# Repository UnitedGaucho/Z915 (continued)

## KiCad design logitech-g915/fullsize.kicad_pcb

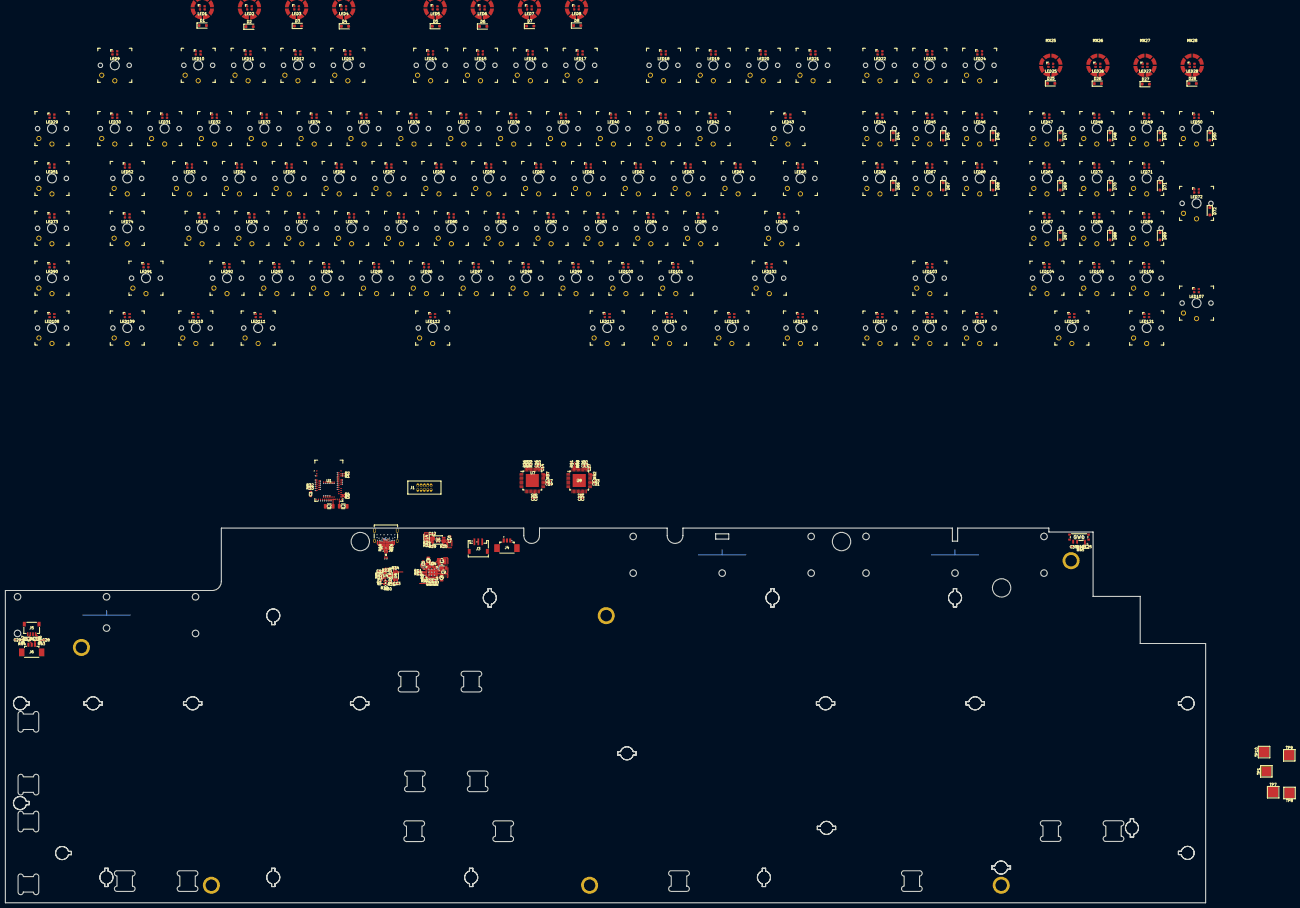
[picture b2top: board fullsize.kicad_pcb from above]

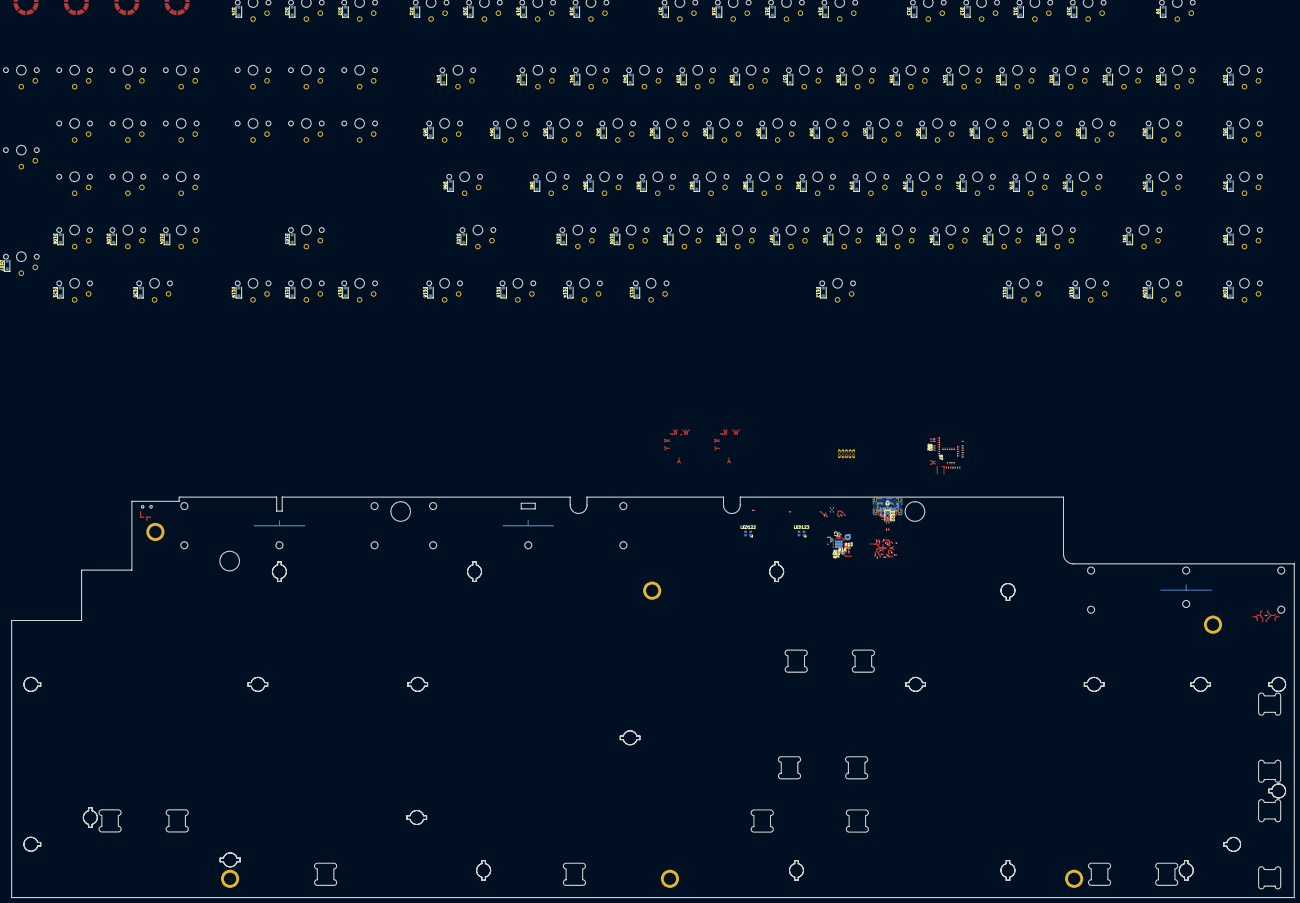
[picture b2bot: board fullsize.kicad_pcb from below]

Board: 4 copper layers, 458.6 x 143.2 mm, 477 parts (104 on the bottom side), 258 nets.

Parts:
C1, C28, C29, C30: 10nF; C_0603_1608Metric
C2, C3: 10uF; C_1206_3216Metric
C4: 47nF; C_0402_1005Metric
C5: 1uF; C_0603_1608Metric
C6, C8: 10uF; C_0805_2012Metric
C7: 4.7uF; C_0402_1005Metric
C9: 22uF; C_0805_2012Metric
C10: 4.7uF; C_0805_2012Metric
C11, C13, C14, C19, C20, C21, C22, C27: 0.1uF; C_0402_1005Metric
C12: 10uF; C_0402_1005Metric
C15, C16, C17, C18, C23, C24, C25, C26: 0.47uF; C_0402_1005Metric
C31: 4.7nF; C_0402_1005Metric
D1, D2, D3, D4, D5, D6, D7, D8, D9, D10, D11, D12, D13, D14, D15, D16, D17, D18, D19, D20, D21, D22, D23, D24, D25, D26, D27, D28, D29, D30, D31, D32, D33, D34, D35, D36, D37, D38, D39, D40, D41, D42, D43, D44, D45, D46, D47, D48, D49, D50, D51, D52, D53, D54, D55, D56, D57, D58, D59, D60, D61, D62, D63, D64, D65, D66, D67, D68, D69, D70, D71, D72, D73, D74, D75, D76, D77, D78, D79, D80, D81, D82, D83, D84, D85, D86, D87, D88, D89, D90, D91, D92, D93, D94, D95, D96, D97, D98, D99, D100, D101, D102, D103, D104, D105, D106, D107, D108, D109, D110, D111, D112, D113, D114, D115, D116, D117, D118, D119, D120, D121: B140S1F-7; D_SOD-123F
D122: SZSMF6L5.0AT3G; D_SOD-123F
D123, D124, D125: ESD5Z3; D_SOD-523
J1: Conn_02x05_Odd_Even; DB_CONN
J3: 648103131822
J4, J6: 10114830-11103LF; AMPHENOL_10114830-11103LF
J5: G846A04100Y1EU; AMPHENOL_G846A04100Y1EU
J7: USB_C_Receptacle_USB2.0_16P; AMPHENOL_GSB1C411101DS1HR
L1: 60R@100MHz; L_0603_1608Metric
L2: L_Coupled; FIL_ACM2012-900-2P-T001
L3: 1.5uH; L_1008_2520Metric
L4: 2.2uH; L_Murata_DFE201610P
LED1, LED2, LED3, LED4, LED5, LED6, LED7, LED8, LED9, LED10, LED11, LED12, LED13, LED14, LED15, LED16, LED17, LED18, LED19, LED20, LED21, LED22, LED23, LED24, LED25, LED26, LED27, LED28, LED29, LED30, LED31, LED32, LED33, LED34, LED35, LED36, LED37, LED38, LED39, LED40, LED41, LED42, LED43, LED44, LED45, LED46, LED47, LED48, LED49, LED50, LED51, LED52, LED53, LED54, LED55, LED56, LED57, LED58, LED59, LED60, LED61, LED62, LED63, LED64, LED65, LED66, LED67, LED68, LED69, LED70, LED71, LED72, LED73, LED74, LED75, LED76, LED77, LED78, LED79, LED80, LED81, LED82, LED83, LED84, LED85, LED86, LED87, LED88, LED89, LED90, LED91, LED92, LED93, LED94, LED95, LED96, LED97, LED98, LED99, LED100, LED101, LED102, LED103, LED104, LED105, LED106, LED107, LED108, LED109, LED110, LED111, LED112, LED113, LED114, LED115, LED116, LED117, LED118, LED119, LED120, LED121, LED122, LED123: ASMB-LTD3; LED_ASMB-LTD3
MX1, MX2, MX3, MX4, MX5, MX6, MX7, MX8, MX25, MX26, MX27, MX28: 1.00u; Membrane-G915
MX9, MX10, MX11, MX12, MX13, MX14, MX15, MX16, MX17, MX18, MX19, MX20, MX21, MX22, MX23, MX24, MX29, MX30, MX31, MX32, MX33, MX34, MX35, MX36, MX37, MX38, MX39, MX40, MX41, MX42, MX43, MX44, MX45, MX46, MX47, MX48, MX49, MX50, MX51, MX52, MX53, MX54, MX55, MX56, MX57, MX58, MX59, MX60, MX61, MX62, MX63, MX64, MX65, MX66, MX67, MX68, MX69, MX70, MX71, MX72, MX73, MX74, MX75, MX76, MX77, MX78, MX79, MX80, MX81, MX82, MX83, MX84, MX85, MX86, MX87, MX88, MX89, MX90, MX91, MX92, MX93, MX94, MX95, MX96, MX97, MX98, MX99, MX100, MX101, MX102, MX103, MX104, MX105, MX106, MX107, MX108, MX109, MX110, MX111, MX112, MX113, MX114, MX115, MX116, MX117, MX118, MX119, MX120, MX121: 1.00u; SW_Kailh_Choc_V1_THT
Q1: NTA4153NT1G; SOT-416
R1, R2, R3, R4: 22; R_0402_1005Metric
R5, R6: 4.7k; R_0402_1005Metric
R7: 10k; R_0402_1005Metric
R8, R9, R26, R27, R28, R30, R43, R44, R45: 100k; R_0402_1005Metric
R10, R11, R12, R13, R17, R20, R21, R23, R24, R25: 0; R_0402_1005Metric
R14: 845; R_0402_1005Metric
R15, R16: 5.1k; R_0402_1005Metric
R18: 5.23k; R_0402_1005Metric
R19: 30.9k; R_0402_1005Metric
R22: 887k; R_0402_1005Metric
R29: 21.5k; R_0402_1005Metric
R31: 316; R_0402_1005Metric
R32: 1M; R_0402_1005Metric
R33: 499k; R_0402_1005Metric
R34: 487; R_0402_1005Metric
R35: 953; R_0402_1005Metric
R36, R38, R39, R40, R41, R49: 100K; R_0402_1005Metric
R37, R42: 20k; R_0402_1005Metric
R46, R47, R48: 1k; R_0402_1005Metric
S1: Open Hardware; OSHW-Logo
S2: BLE-symbol
S3: ZMK_logo
SW1: PCM12SMTR; SW_PCM12SMTR
TP1, TP7, TP8, TP9, TP10: TouchPoint; TestPoint_Pad_4.0x4.0mm
U1: MDBT50Q-1MV2/MEN; Raytac_MDBT50Q
U2: BQ25616J; Texas_RTW_WQFN-24-1EP_4x4mm_P0.5mm_EP2.7x2.7mm_ThermalVias
U3: TPD4E05U06DQAR; USON-10
U4: TUSB320; Texas_X2QFN-12_1.6x1.6mm_P0.4mm
U5: TPS62842DGR; HVSSOP-8-1EP_3x3mm_P0.65mm_EP1.57x1.89mm
U6: TS5A23167; VSSOP-8_2.3x2mm_P0.5mm
U7, U8: IS31FL3733-TQ; TQFP-48-1EP_7x7mm_P0.5mm_EP5x5mm

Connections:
+3V0: C2.1, C11.2, C12.1, C13.1, C14.1, C15.1, C16.1, C25.1, C26.1, C27.1, J1.1, L4.2, R5.2, R6.2, R7.2, R26.2, R27.2, R28.2, R39.2, R40.2, R43.2, R44.2, R45.2, U1.28 (VDD), U1.30 (VDDH), U4.12 (VDD), U5.1 (VOS), U6.8 (V+), U7.37 (AVCC), U7.38 (DVCC), U7.39 (VIO), U8.37 (AVCC), U8.38 (DVCC), U8.39 (VIO)
/COL1: MX29.2 (B), MX51.2 (B), MX73.2 (B), MX90.2 (B), MX108.2 (B), U1.3 (P1.10)
/COL2: MX9.2 (B), MX30.2 (B), MX52.2 (B), MX74.2 (B), MX91.2 (B), MX109.2 (B), MX110.2 (B), U1.4 (P1.11)
/COL3: MX31.2 (B), MX53.2 (B), MX75.2 (B), MX92.2 (B), MX111.2 (B), U1.5 (P1.12)
/COL4: MX10.2 (B), MX32.2 (B), MX54.2 (B), MX76.2 (B), MX93.2 (B), U1.6 (P1.13)
/COL5: MX11.2 (B), MX33.2 (B), MX55.2 (B), MX77.2 (B), MX94.2 (B), U1.7 (P1.14)
/COL6: MX12.2 (B), MX34.2 (B), MX56.2 (B), MX78.2 (B), MX95.2 (B), U1.8 (P1.15)
/COL7: MX13.2 (B), MX35.2 (B), MX57.2 (B), MX79.2 (B), MX96.2 (B), MX112.2 (B), U1.9 (P0.03)
/COL8: MX36.2 (B), MX58.2 (B), MX80.2 (B), MX97.2 (B), U1.10 (P0.29)
/COL9: MX14.2 (B), MX37.2 (B), MX59.2 (B), MX81.2 (B), MX98.2 (B), U1.11 (P0.02)
/COL10: MX15.2 (B), MX38.2 (B), MX60.2 (B), MX82.2 (B), MX99.2 (B), MX113.2 (B), U1.12 (P0.31)
/COL11: MX16.2 (B), MX39.2 (B), MX61.2 (B), MX83.2 (B), MX100.2 (B), MX114.2 (B), U1.13 (P0.28)
/COL12: MX17.2 (B), MX40.2 (B), MX62.2 (B), MX84.2 (B), MX101.2 (B), U1.16 (P0.27)
/COL13: MX18.2 (B), MX41.2 (B), MX63.2 (B), MX85.2 (B), MX115.2 (B), U1.17 (P0.00)
/COL14: MX19.2 (B), MX42.2 (B), MX64.2 (B), MX86.2 (B), MX102.2 (B), MX116.2 (B), U1.18 (P0.01)
/COL15: MX20.2 (B), MX21.2 (B), MX43.2 (B), MX65.2 (B), U1.19 (P0.26)
/COL16: MX22.2 (B), MX44.2 (B), MX66.2 (B), MX117.2 (B), U1.20 (P0.04)
/COL17: MX23.2 (B), MX45.2 (B), MX67.2 (B), MX103.2 (B), MX118.2 (B), U1.21 (P0.05)
/COL18: MX24.2 (B), MX46.2 (B), MX68.2 (B), MX119.2 (B), U1.22 (P0.06)
/COL19: MX47.2 (B), MX69.2 (B), MX87.2 (B), MX104.2 (B), MX120.2 (B), U1.23 (P0.07)
/COL20: MX48.2 (B), MX70.2 (B), MX88.2 (B), MX105.2 (B), U1.24 (P0.08)
/COL21: MX49.2 (B), MX71.2 (B), MX89.2 (B), MX106.2 (B), MX121.2 (B), U1.25 (P1.08)
/COL22: MX50.2 (B), MX72.2 (B), MX107.2 (B), U1.26 (P1.09)
/DB_SWDCLK: J1.4, R2.1
/DB_SWDIO: J1.2, R1.1
/INTB1: R39.1, U1.48 (P0.24), U7.45 (~INTB)
/INTB2: R40.1, U1.49 (P0.25), U8.45 (~INTB)
/NRF_D+: R4.2, U1.35 (D+)
/NRF_D-: R3.2, U1.34 (D-)
/PWR: C30.1, R45.1, R48.1, U1.50 (P1.02)
/ROW0: D9.1 (K), D10.1 (K), D11.1 (K), D12.1 (K), D13.1 (K), D14.1 (K), D15.1 (K), D16.1 (K), D17.1 (K), D18.1 (K), D19.1 (K), D20.1 (K), D21.1 (K), D22.1 (K), D23.1 (K), D24.1 (K), U1.56 (P1.04)
/ROW1: D29.1 (K), D30.1 (K), D31.1 (K), D32.1 (K), D33.1 (K), D34.1 (K), D35.1 (K), D36.1 (K), D37.1 (K), D38.1 (K), D39.1 (K), D40.1 (K), D41.1 (K), D42.1 (K), D43.1 (K), D44.1 (K), D45.1 (K), D46.1 (K), D47.1 (K), D48.1 (K), D49.1 (K), D50.1 (K), U1.57 (P1.06)
/ROW2: D51.1 (K), D52.1 (K), D53.1 (K), D54.1 (K), D55.1 (K), D56.1 (K), D57.1 (K), D58.1 (K), D59.1 (K), D60.1 (K), D61.1 (K), D62.1 (K), D63.1 (K), D64.1 (K), D65.1 (K), D66.1 (K), D67.1 (K), D68.1 (K), D69.1 (K), D70.1 (K), D71.1 (K), D72.1 (K), U1.58 (P1.07)
/ROW3: D73.1 (K), D74.1 (K), D75.1 (K), D76.1 (K), D77.1 (K), D78.1 (K), D79.1 (K), D80.1 (K), D81.1 (K), D82.1 (K), D83.1 (K), D84.1 (K), D85.1 (K), D86.1 (K), D87.1 (K), D88.1 (K), D89.1 (K), U1.59 (P1.05)
/ROW4: D90.1 (K), D91.1 (K), D92.1 (K), D93.1 (K), D94.1 (K), D95.1 (K), D96.1 (K), D97.1 (K), D98.1 (K), D99.1 (K), D100.1 (K), D101.1 (K), D102.1 (K), D103.1 (K), D104.1 (K), D105.1 (K), D106.1 (K), D107.1 (K), U1.60 (P1.03)
/ROW5: D108.1 (K), D109.1 (K), D110.1 (K), D111.1 (K), D112.1 (K), D113.1 (K), D114.1 (K), D115.1 (K), D116.1 (K), D117.1 (K), D118.1 (K), D119.1 (K), D120.1 (K), D121.1 (K), U1.61 (P1.01)
/ROWM: D1.1 (K), D2.1 (K), D3.1 (K), D4.1 (K), D5.1 (K), D6.1 (K), D7.1 (K), D8.1 (K), D25.1 (K), D26.1 (K), D27.1 (K), D28.1 (K), U1.47 (P1.00)
/SCL: R6.1, U1.46 (P0.22), U7.42 (SCL), U8.42 (SCL), U8.43 (ADDR1)
/SDA: R5.1, U1.45 (P0.23), U7.41 (SDA), U8.41 (SDA)
/SDB: R38.2, R49.2, U1.44 (P0.20), U7.46 (~SDB), U8.46 (~SDB)
/USB and Power Mgmt/BATT_NTC: C31.1, J3.2, J4.3, R18.1, R19.2, U2.11 (TS)
/USB and Power Mgmt/CC1: J7.A5 (CC1), R15.2, R20.2, U3.5 (D2-), U3.6 (NC)
/USB and Power Mgmt/CC2: J7.B5 (CC2), R16.2, R21.2, U3.1 (IO1), U3.10 (NC)
/USB and Power Mgmt/ILIM: R35.2, U2.8 (ILIM), U6.1
/USB and Power Mgmt/OUT1: R26.1, U4.7 (SDA/OUT1), U6.7
/USB and Power Mgmt/OUT2: R28.1, U4.8 (SCL/OUT2), U6.3
/USB and Power Mgmt/REGN: C7.1, R18.2, U2.22 (REGN)
/USB and Power Mgmt/TVS_D+: J7.A6 (D+), J7.B6 (D+), L2.2, U3.2 (IO2), U3.9 (NC)
/USB and Power Mgmt/TVS_D-: J7.A7 (D-), J7.B7 (D-), L2.1, U3.4 (D2+), U3.7 (NC)
/USB and Power Mgmt/U2-D+: R11.1, U2.3 (D+)
/USB and Power Mgmt/U2-D-: R12.1, U2.4 (D-)
/USB_D+: L2.3, R4.1, R11.2
/USB_D-: L2.4, R3.1, R12.2
/VBATT_nRF: C1.1, R32.1, R33.2, U1.14 (AIN6)
/VBUS: C3.1, C5.1, D122.1 (K), J1.5, J7.A4B9 (VBUS), J7.B4A9 (VBUS), Q1.G, R22.2, R30.2, U1.32 (VBUS), U2.1 (VAC), U2.24 (VBUS)
/VCOM-UART_RX: J1.8, U1.43 (P0.21)
/VCOM-UART_TX: J1.7, U1.42 (P0.19)
/VOL_A: C28.1, R43.1, R46.1, U1.52 (P0.09)
/VOL_B: C29.1, R44.1, R47.1, U1.54 (P0.10)
/indicators_controls/Vol_A: D123.1 (K), J5.1, J6.3, R46.2
/indicators_controls/Vol_B: D124.1 (K), J5.3, J6.2, R47.2
/rgb-led_matrix/C1.1: LED29.1 (A), LED30.1 (A), LED51.1 (A), LED52.1 (A), U7.16 (CS1)
/rgb-led_matrix/C1.2: LED9.1 (A), LED31.1 (A), LED53.1 (A), U7.17 (CS2)
/rgb-led_matrix/C1.3: LED1.1 (A), LED10.1 (A), LED32.1 (A), LED54.1 (A), U7.18 (CS3)
/rgb-led_matrix/C1.4: LED2.1 (A), LED11.1 (A), LED33.1 (A), LED55.1 (A), U7.19 (CS4)
/rgb-led_matrix/C1.5: LED3.1 (A), LED12.1 (A), LED34.1 (A), LED56.1 (A), U7.21 (CS5)
/rgb-led_matrix/C1.6: LED4.1 (A), LED13.1 (A), LED35.1 (A), LED57.1 (A), U7.22 (CS6)
/rgb-led_matrix/C1.7: LED5.1 (A), LED14.1 (A), LED36.1 (A), LED58.1 (A), U7.23 (CS7)
/rgb-led_matrix/C1.8: LED6.1 (A), LED15.1 (A), LED37.1 (A), LED59.1 (A), U7.24 (CS8)
/rgb-led_matrix/C1.9: LED7.1 (A), LED16.1 (A), LED38.1 (A), LED60.1 (A), U7.25 (CS9)
/rgb-led_matrix/C1.10: LED8.1 (A), LED17.1 (A), LED39.1 (A), LED61.1 (A), U7.26 (CS10)
/rgb-led_matrix/C1.11: LED40.1 (A), LED41.1 (A), LED62.1 (A), LED63.1 (A), U7.27 (CS11)
/rgb-led_matrix/C1.12: LED18.1 (A), LED19.1 (A), LED122.1 (A), LED123.1 (A), U7.28 (CS12)
/rgb-led_matrix/C1.13: LED20.1 (A), LED21.1 (A), LED42.1 (A), LED64.1 (A), U7.30 (CS13)
/rgb-led_matrix/C1.14: LED22.1 (A), LED43.1 (A), LED44.1 (A), LED65.1 (A), U7.31 (CS14)
/rgb-led_matrix/C1.15: LED23.1 (A), LED45.1 (A), LED67.1 (A), LED103.1 (A), U7.32 (CS15)
/rgb-led_matrix/C1.16: LED66.1 (A), LED117.1 (A), LED118.1 (A), U7.33 (CS16)
/rgb-led_matrix/C2.1: LED73.1 (A), LED90.1 (A), LED108.1 (A), LED109.1 (A), U8.16 (CS1)
/rgb-led_matrix/C2.2: LED74.1 (A), LED91.1 (A), LED110.1 (A), LED111.1 (A), U8.17 (CS2)
/rgb-led_matrix/C2.3: LED75.1 (A), LED76.1 (A), LED92.1 (A), LED93.1 (A), U8.18 (CS3)
/rgb-led_matrix/C2.4: LED77.1 (A), LED78.1 (A), LED94.1 (A), LED95.1 (A), U8.19 (CS4)
/rgb-led_matrix/C2.5: LED79.1 (A), LED80.1 (A), LED96.1 (A), LED97.1 (A), U8.21 (CS5)
/rgb-led_matrix/C2.6: LED81.1 (A), LED82.1 (A), LED98.1 (A), LED99.1 (A), U8.22 (CS6)
/rgb-led_matrix/C2.7: LED83.1 (A), LED84.1 (A), LED100.1 (A), LED101.1 (A), U8.23 (CS7)
/rgb-led_matrix/C2.8: LED112.1 (A), LED113.1 (A), LED114.1 (A), LED115.1 (A), U8.24 (CS8)
/rgb-led_matrix/C2.9: LED85.1 (A), LED86.1 (A), LED102.1 (A), LED116.1 (A), U8.25 (CS9)
/rgb-led_matrix/C2.10: LED24.1 (A), LED46.1 (A), LED68.1 (A), LED119.1 (A), U8.26 (CS10)
/rgb-led_matrix/C2.11: LED25.1 (A), LED47.1 (A), LED69.1 (A), LED87.1 (A), U8.27 (CS11)
/rgb-led_matrix/C2.12: LED26.1 (A), LED48.1 (A), LED70.1 (A), LED88.1 (A), U8.28 (CS12)
/rgb-led_matrix/C2.13: LED27.1 (A), LED49.1 (A), LED71.1 (A), LED89.1 (A), U8.30 (CS13)
/rgb-led_matrix/C2.14: LED28.1 (A), LED50.1 (A), LED72.1 (A), LED107.1 (A), U8.31 (CS14)
/rgb-led_matrix/C2.15: LED104.1 (A), LED105.1 (A), LED106.1 (A), LED120.1 (A), U8.32 (CS15)
/rgb-led_matrix/C2.16: LED121.1 (A), U8.33 (CS16)
/rgb-led_matrix/S1.1: LED1.2 (RK), LED2.2 (RK), LED3.2 (RK), LED4.2 (RK), LED5.2 (RK), LED6.2 (RK), LED7.2 (RK), LED8.2 (RK), LED18.2 (RK), LED23.2 (RK), LED29.2 (RK), LED40.2 (RK), LED42.2 (RK), LED43.2 (RK), LED66.2 (RK), U7.2 (SW1)
/rgb-led_matrix/S1.2: LED1.3 (GK), LED2.3 (GK), LED3.3 (GK), LED4.3 (GK), LED5.3 (GK), LED6.3 (GK), LED7.3 (GK), LED8.3 (GK), LED18.3 (GK), LED23.3 (GK), LED29.3 (GK), LED40.3 (GK), LED42.3 (GK), LED43.3 (GK), LED66.3 (GK), U7.3 (SW2)
/rgb-led_matrix/S1.3: LED1.4 (BK), LED2.4 (BK), LED3.4 (BK), LED4.4 (BK), LED5.4 (BK), LED6.4 (BK), LED7.4 (BK), LED8.4 (BK), LED18.4 (BK), LED23.4 (BK), LED29.4 (BK), LED40.4 (BK), LED42.4 (BK), LED43.4 (BK), LED66.4 (BK), U7.4 (SW3)
/rgb-led_matrix/S1.4: LED9.2 (RK), LED10.2 (RK), LED11.2 (RK), LED12.2 (RK), LED13.2 (RK), LED14.2 (RK), LED15.2 (RK), LED16.2 (RK), LED17.2 (RK), LED19.2 (RK), LED20.2 (RK), LED45.2 (RK), LED51.2 (RK), LED62.2 (RK), LED65.2 (RK), LED117.2 (RK), U7.6 (SW4)
/rgb-led_matrix/S1.5: LED9.3 (GK), LED10.3 (GK), LED11.3 (GK), LED12.3 (GK), LED13.3 (GK), LED14.3 (GK), LED15.3 (GK), LED16.3 (GK), LED17.3 (GK), LED19.3 (GK), LED20.3 (GK), LED45.3 (GK), LED51.3 (GK), LED62.3 (GK), LED65.3 (GK), LED117.3 (GK), U7.7 (SW5)
/rgb-led_matrix/S1.6: LED9.4 (BK), LED10.4 (BK), LED11.4 (BK), LED12.4 (BK), LED13.4 (BK), LED14.4 (BK), LED15.4 (BK), LED16.4 (BK), LED17.4 (BK), LED19.4 (BK), LED20.4 (BK), LED45.4 (BK), LED51.4 (BK), LED62.4 (BK), LED65.4 (BK), LED117.4 (BK), U7.8 (SW6)
/rgb-led_matrix/S1.7: LED21.2 (RK), LED22.2 (RK), LED31.2 (RK), LED32.2 (RK), LED33.2 (RK), LED34.2 (RK), LED35.2 (RK), LED36.2 (RK), LED37.2 (RK), LED38.2 (RK), LED39.2 (RK), LED52.2 (RK), LED63.2 (RK), LED67.2 (RK), LED118.2 (RK), LED122.2 (RK), U7.9 (SW7)
/rgb-led_matrix/S1.8: LED21.3 (GK), LED22.3 (GK), LED31.3 (GK), LED32.3 (GK), LED33.3 (GK), LED34.3 (GK), LED35.3 (GK), LED36.3 (GK), LED37.3 (GK), LED38.3 (GK), LED39.3 (GK), LED52.3 (GK), LED63.3 (GK), LED67.3 (GK), LED118.3 (GK), LED122.3 (GK), U7.10 (SW8)
/rgb-led_matrix/S1.9: LED21.4 (BK), LED22.4 (BK), LED31.4 (BK), LED32.4 (BK), LED33.4 (BK), LED34.4 (BK), LED35.4 (BK), LED36.4 (BK), LED37.4 (BK), LED38.4 (BK), LED39.4 (BK), LED52.4 (BK), LED63.4 (BK), LED67.4 (BK), LED118.4 (BK), LED122.4 (BK), U7.11 (SW9)
/rgb-led_matrix/S1.10: LED30.2 (RK), LED41.2 (RK), LED44.2 (RK), LED53.2 (RK), LED54.2 (RK), LED55.2 (RK), LED56.2 (RK), LED57.2 (RK), LED58.2 (RK), LED59.2 (RK), LED60.2 (RK), LED61.2 (RK), LED64.2 (RK), LED103.2 (RK), LED123.2 (RK), U7.13 (SW10)
/rgb-led_matrix/S1.11: LED30.3 (GK), LED41.3 (GK), LED44.3 (GK), LED53.3 (GK), LED54.3 (GK), LED55.3 (GK), LED56.3 (GK), LED58.3 (GK), LED59.3 (GK), LED60.3 (GK), LED61.3 (GK), LED64.3 (GK), LED103.3 (GK), LED123.3 (GK), U7.14 (SW11)
/rgb-led_matrix/S1.12: LED30.4 (BK), LED41.4 (BK), LED44.4 (BK), LED53.4 (BK), LED54.4 (BK), LED55.4 (BK), LED56.4 (BK), LED58.4 (BK), LED59.4 (BK), LED60.4 (BK), LED61.4 (BK), LED64.4 (BK), LED103.4 (BK), LED123.4 (BK), U7.15 (SW12)
/rgb-led_matrix/S2.1: LED24.2 (RK), LED25.2 (RK), LED26.2 (RK), LED27.2 (RK), LED28.2 (RK), LED73.2 (RK), LED74.2 (RK), LED75.2 (RK), LED77.2 (RK), LED79.2 (RK), LED81.2 (RK), LED83.2 (RK), LED85.2 (RK), LED104.2 (RK), LED112.2 (RK), LED121.2 (RK), U8.2 (SW1)
/rgb-led_matrix/S2.2: LED24.3 (GK), LED25.3 (GK), LED26.3 (GK), LED27.3 (GK), LED28.3 (GK), LED73.3 (GK), LED74.3 (GK), LED75.3 (GK), LED77.3 (GK), LED79.3 (GK), LED81.3 (GK), LED83.3 (GK), LED85.3 (GK), LED104.3 (GK), LED112.3 (GK), LED121.3 (GK), U8.3 (SW2)
/rgb-led_matrix/S2.3: LED24.4 (BK), LED25.4 (BK), LED26.4 (BK), LED27.4 (BK), LED28.4 (BK), LED73.4 (BK), LED74.4 (BK), LED75.4 (BK), LED77.4 (BK), LED79.4 (BK), LED81.4 (BK), LED83.4 (BK), LED85.4 (BK), LED104.4 (BK), LED112.4 (BK), LED121.4 (BK), U8.4 (SW3)
/rgb-led_matrix/S2.4: LED46.2 (RK), LED47.2 (RK), LED48.2 (RK), LED49.2 (RK), LED50.2 (RK), LED86.2 (RK), LED90.2 (RK), LED91.2 (RK), LED92.2 (RK), LED94.2 (RK), LED96.2 (RK), LED98.2 (RK), LED100.2 (RK), LED113.2 (RK), LED120.2 (RK), U8.6 (SW4)
/rgb-led_matrix/S2.5: LED46.3 (GK), LED47.3 (GK), LED48.3 (GK), LED49.3 (GK), LED50.3 (GK), LED86.3 (GK), LED90.3 (GK), LED91.3 (GK), LED92.3 (GK), LED94.3 (GK), LED96.3 (GK), LED98.3 (GK), LED100.3 (GK), LED113.3 (GK), LED120.3 (GK), U8.7 (SW5)
/rgb-led_matrix/S2.6: LED46.4 (BK), LED47.4 (BK), LED48.4 (BK), LED49.4 (BK), LED50.4 (BK), LED86.4 (BK), LED90.4 (BK), LED91.4 (BK), LED92.4 (BK), LED94.4 (BK), LED96.4 (BK), LED98.4 (BK), LED100.4 (BK), LED113.4 (BK), LED120.4 (BK), U8.8 (SW6)
/rgb-led_matrix/S2.7: LED68.2 (RK), LED69.2 (RK), LED70.2 (RK), LED71.2 (RK), LED72.2 (RK), LED93.2 (RK), LED95.2 (RK), LED97.2 (RK), LED99.2 (RK), LED101.2 (RK), LED102.2 (RK), LED105.2 (RK), LED108.2 (RK), LED110.2 (RK), LED114.2 (RK), U8.9 (SW7)
/rgb-led_matrix/S2.8: LED68.3 (GK), LED69.3 (GK), LED70.3 (GK), LED71.3 (GK), LED72.3 (GK), LED93.3 (GK), LED95.3 (GK), LED97.3 (GK), LED99.3 (GK), LED101.3 (GK), LED102.3 (GK), LED105.3 (GK), LED108.3 (GK), LED110.3 (GK), LED114.3 (GK), U8.10 (SW8)
/rgb-led_matrix/S2.9: LED68.4 (BK), LED69.4 (BK), LED70.4 (BK), LED71.4 (BK), LED72.4 (BK), LED93.4 (BK), LED95.4 (BK), LED97.4 (BK), LED99.4 (BK), LED101.4 (BK), LED102.4 (BK), LED105.4 (BK), LED108.4 (BK), LED110.4 (BK), LED114.4 (BK), U8.11 (SW9)
/rgb-led_matrix/S2.10: LED76.2 (RK), LED78.2 (RK), LED80.2 (RK), LED82.2 (RK), LED84.2 (RK), LED87.2 (RK), LED88.2 (RK), LED89.2 (RK), LED106.2 (RK), LED107.2 (RK), LED109.2 (RK), LED111.2 (RK), LED115.2 (RK), LED116.2 (RK), LED119.2 (RK), U8.13 (SW10)
/rgb-led_matrix/S2.11: LED76.3 (GK), LED78.3 (GK), LED80.3 (GK), LED82.3 (GK), LED84.3 (GK), LED87.3 (GK), LED88.3 (GK), LED89.3 (GK), LED106.3 (GK), LED107.3 (GK), LED109.3 (GK), LED111.3 (GK), LED115.3 (GK), LED116.3 (GK), LED119.3 (GK), U8.14 (SW11)
/rgb-led_matrix/S2.12: LED76.4 (BK), LED78.4 (BK), LED80.4 (BK), LED82.4 (BK), LED84.4 (BK), LED87.4 (BK), LED88.4 (BK), LED89.4 (BK), LED106.4 (BK), LED107.4 (BK), LED109.4 (BK), LED111.4 (BK), LED115.4 (BK), LED116.4 (BK), LED119.4 (BK), U8.15 (SW12)
/rgb-led_matrix/SYNC: U7.40 (SYNC), U8.40 (SYNC)
/~nReset: J1.10, R7.1, U1.40 (~RESET)
BAT: C6.1, J3.1, J4.1, R32.2, U2.13 (BAT), U2.14 (BAT)
GND: C1.2, C2.2, C3.2, C5.2, C6.2, C7.2, C8.2, C9.2, C10.2, C11.1, C12.2, C13.2, C14.2, C15.2, C16.2, C17.2, C18.2, C19.2, C20.2, C21.2, C22.2, C23.2, C24.2, C25.2, C26.2, C27.2, C28.2, C29.2, C30.2, C31.2, D122.2 (A), D123.2 (A), D124.2 (A), D125.2 (A), J1.3, J3.3, J3.SH (Shield), J4.2, J4.SH (Shield), J5.2, J5.4, J5.SH (Shield), J6.1, J6.SH (Shield), J7.A1B12 (GND), J7.B1A12 (GND), L1.1, Q1.S, R10.2, R13.2, R14.2, R15.1, R16.1, R17.1, R19.1, R24.1, R29.1, R30.1, R31.1, R33.1, R34.1, R35.1, R36.1, R37.2, R38.1, R41.1, R42.2, R49.1, SW1.2 (B), SW1.SH, TP1.1 (GND), TP7.1 (GND), TP8.1 (GND), TP9.1 (GND), TP10.1 (GND), U1.1 (GND), U1.2 (GND), U1.15 (GND), U1.33 (GND), U1.55 (GND), U2.17 (GND), U2.18 (GND), U2.25 (GND), U3.3 (GND), U3.8 (GND), U4.3 (PORT), U4.10 (GND), U5.8 (GND), U5.9 (EP), U6.4 (V-), U7.5 (PGND), U7.12 (PGND), U7.34 (AGND), U7.43 (ADDR1), U7.44 (ADDR2), U7.48 (GND), U7.49 (GND), U8.5 (PGND), U8.12 (PGND), U8.34 (AGND), U8.44 (ADDR2), U8.48 (GND), U8.49 (GND)
GNDPWR: J7.SH (SHIELD), L1.2
unnamed: C4.2, L3.1, U2.19 (SW), U2.20 (SW)
unnamed: D9.2 (A), MX9.1 (A)
unnamed: D10.2 (A), MX10.1 (A)
unnamed: D11.2 (A), MX11.1 (A)
unnamed: D12.2 (A), MX12.1 (A)
unnamed: D13.2 (A), MX13.1 (A)
unnamed: D14.2 (A), MX14.1 (A)
unnamed: D15.2 (A), MX15.1 (A)
unnamed: D16.2 (A), MX16.1 (A)
unnamed: D17.2 (A), MX17.1 (A)
unnamed: D18.2 (A), MX18.1 (A)
unnamed: D19.2 (A), MX19.1 (A)
unnamed: D20.2 (A), MX20.1 (A)
unnamed: D21.2 (A), MX21.1 (A)
unnamed: D22.2 (A), MX22.1 (A)
unnamed: D23.2 (A), MX23.1 (A)
unnamed: D24.2 (A), MX24.1 (A)
unnamed: D29.2 (A), MX29.1 (A)
unnamed: D30.2 (A), MX30.1 (A)
unnamed: D31.2 (A), MX31.1 (A)
unnamed: D32.2 (A), MX32.1 (A)
unnamed: D33.2 (A), MX33.1 (A)
unnamed: D34.2 (A), MX34.1 (A)
unnamed: D35.2 (A), MX35.1 (A)
unnamed: D36.2 (A), MX36.1 (A)
unnamed: D37.2 (A), MX37.1 (A)
unnamed: D38.2 (A), MX38.1 (A)
unnamed: D39.2 (A), MX39.1 (A)
unnamed: D40.2 (A), MX40.1 (A)
unnamed: D41.2 (A), MX41.1 (A)
unnamed: D42.2 (A), MX42.1 (A)
unnamed: D43.2 (A), MX43.1 (A)
unnamed: D44.2 (A), MX44.1 (A)
unnamed: D45.2 (A), MX45.1 (A)
unnamed: D46.2 (A), MX46.1 (A)
unnamed: D47.2 (A), MX47.1 (A)
unnamed: D48.2 (A), MX48.1 (A)
unnamed: D49.2 (A), MX49.1 (A)
unnamed: D50.2 (A), MX50.1 (A)
unnamed: D51.2 (A), MX51.1 (A)
unnamed: D52.2 (A), MX52.1 (A)
unnamed: D53.2 (A), MX53.1 (A)
unnamed: D54.2 (A), MX54.1 (A)
unnamed: D55.2 (A), MX55.1 (A)
unnamed: D56.2 (A), MX56.1 (A)
unnamed: D57.2 (A), MX57.1 (A)
unnamed: D58.2 (A), MX58.1 (A)
unnamed: D59.2 (A), MX59.1 (A)
unnamed: D60.2 (A), MX60.1 (A)
unnamed: D61.2 (A), MX61.1 (A)
unnamed: D62.2 (A), MX62.1 (A)
unnamed: D63.2 (A), MX63.1 (A)
unnamed: D64.2 (A), MX64.1 (A)
unnamed: D65.2 (A), MX65.1 (A)
unnamed: D66.2 (A), MX66.1 (A)
unnamed: D67.2 (A), MX67.1 (A)
unnamed: D68.2 (A), MX68.1 (A)
unnamed: D69.2 (A), MX69.1 (A)
unnamed: D70.2 (A), MX70.1 (A)
unnamed: D71.2 (A), MX71.1 (A)
unnamed: D72.2 (A), MX72.1 (A)
unnamed: D73.2 (A), MX73.1 (A)
unnamed: D74.2 (A), MX74.1 (A)
unnamed: D75.2 (A), MX75.1 (A)
unnamed: D76.2 (A), MX76.1 (A)
unnamed: D77.2 (A), MX77.1 (A)
unnamed: D78.2 (A), MX78.1 (A)
unnamed: D79.2 (A), MX79.1 (A)
unnamed: D80.2 (A), MX81.1 (A)
unnamed: D81.2 (A), MX80.1 (A)
unnamed: D82.2 (A), MX82.1 (A)
unnamed: D83.2 (A), MX83.1 (A)
unnamed: D84.2 (A), MX84.1 (A)
unnamed: D85.2 (A), MX85.1 (A)
unnamed: D86.2 (A), MX86.1 (A)
unnamed: D87.2 (A), MX87.1 (A)
unnamed: D88.2 (A), MX88.1 (A)
unnamed: D89.2 (A), MX89.1 (A)
unnamed: D90.2 (A), MX90.1 (A)
unnamed: D91.2 (A), MX91.1 (A)
unnamed: D92.2 (A), MX92.1 (A)
unnamed: D93.2 (A), MX93.1 (A)
unnamed: D94.2 (A), MX94.1 (A)
unnamed: D95.2 (A), MX95.1 (A)
unnamed: D96.2 (A), MX96.1 (A)
unnamed: D97.2 (A), MX97.1 (A)
unnamed: D98.2 (A), MX98.1 (A)
unnamed: D99.2 (A), MX99.1 (A)
unnamed: D100.2 (A), MX100.1 (A)
unnamed: D101.2 (A), MX101.1 (A)
unnamed: D102.2 (A), MX102.1 (A)
unnamed: D103.2 (A), MX103.1 (A)
unnamed: D104.2 (A), MX104.1 (A)
unnamed: D105.2 (A), MX105.1 (A)
unnamed: D106.2 (A), MX106.1 (A)
unnamed: D107.2 (A), MX107.1 (A)
unnamed: D108.2 (A), MX108.1 (A)
unnamed: D109.2 (A), MX109.1 (A)
unnamed: D110.2 (A), MX110.1 (A)
unnamed: D111.2 (A), MX111.1 (A)
unnamed: D112.2 (A), MX112.1 (A)
unnamed: D113.2 (A), MX113.1 (A)
unnamed: D114.2 (A), MX114.1 (A)
unnamed: D115.2 (A), MX115.1 (A)
unnamed: D116.2 (A), MX116.1 (A)
unnamed: D117.2 (A), MX117.1 (A)
unnamed: D118.2 (A), MX118.1 (A)
unnamed: D119.2 (A), MX119.1 (A)
unnamed: D120.2 (A), MX120.1 (A)
unnamed: D121.2 (A), MX121.1 (A)
unnamed: D125.1 (K), R48.2, SW1.1 (A)
unnamed: R31.2, U6.6
unnamed: R34.2, U6.2, U6.5
unnamed: R2.2, U1.53 (SWDCLK)
unnamed: R1.2, U1.51 (SWDIO)
unnamed: C4.1, U2.21 (BTST)
unnamed: R14.1, U2.10 (ICHG)
unnamed: R13.1, U2.6 (OTG)
unnamed: R9.2, U2.7 (PG)
unnamed: C8.1, U2.23 (PMID)
unnamed: R8.2, U2.5 (STAT)
unnamed: R17.2, U2.12 (VSET)
unnamed: R10.1, U2.9 (~CE)
unnamed: R20.1, U4.1 (CC1)
unnamed: R21.1, U4.2 (CC2)
unnamed: R22.1, U4.4 (VBUS_DET)
unnamed: Q1.D, R27.1, U4.11 (~EN)
unnamed: R25.1, U5.5 (EN)
unnamed: R23.1, R24.2, U5.3 (MODE)
unnamed: L4.1, U5.2 (SW)
unnamed: R29.2, U5.4 (VSET)
unnamed: R36.2, U7.47 (IICRST)
unnamed: R37.1, U7.35 (RSET)
unnamed: R41.2, U8.47 (IICRST)
unnamed: R42.1, U8.35 (RSET)
VSYS: C9.1, C10.1, C17.1, C18.1, C19.1, C20.1, C21.1, C22.1, C23.1, C24.1, L3.2, R8.1, R9.1, R23.2, R25.2, U2.15 (SYS), U2.16 (SYS), U5.6 (VIN), U7.20 (PVCC), U7.29 (PVCC), U8.20 (PVCC), U8.29 (PVCC)

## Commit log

2026-06-24 Fix readme formatting
2026-06-27 Ignore .history directory
